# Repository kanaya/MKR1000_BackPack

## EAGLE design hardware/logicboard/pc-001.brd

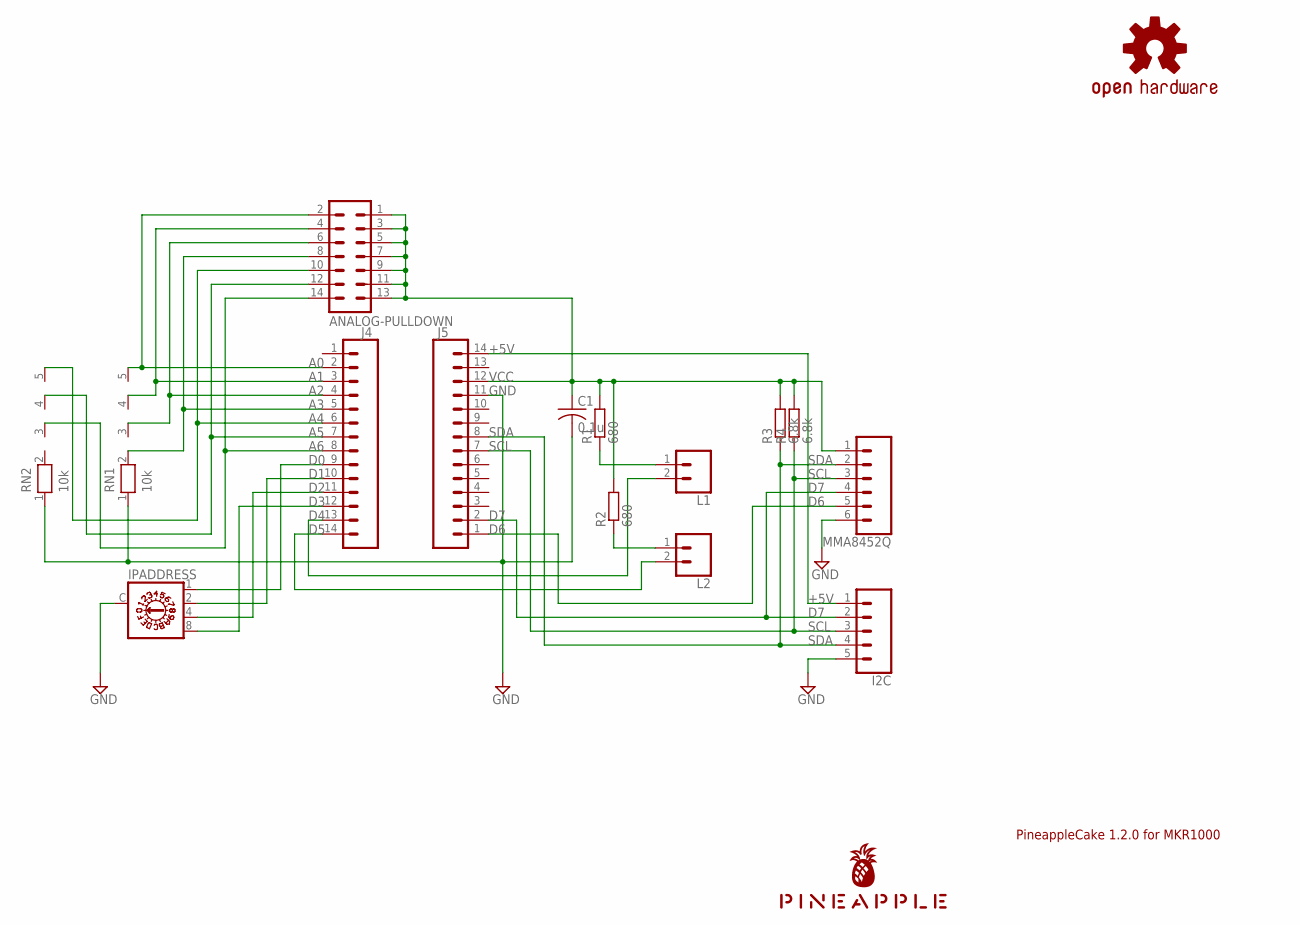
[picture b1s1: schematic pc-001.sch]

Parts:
ANALOG-PULLDOWN: ML14L
C1: 0.1u; C025-025X050
I2C: CONN_05SMD; 1X05_1MM
IPADDRESS: A1353HEX
J4, J5: DNP; 1X14
L1, L2: CONN_02-JST-2-PTH-NO_SILK; JST-2-PTH-NS
LOGO1: OSHW-LOGOS-COPPER; OSHW-LOGO-S_COPPER
MMA8452Q: CONN_06NO_SILK_FEMALE_PTH; 1X06_NO_SILK
R1, R2: 680; 0204/5
R3, R4: 6.8k; 0204/5
RN1, RN2: 10k; RN-5
U$1: PINEAPPLE450

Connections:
+5V: I2C.1, J5.14
A0: ANALOG-PULLDOWN.2, J4.2, RN1.5
A1: ANALOG-PULLDOWN.4, J4.3, RN1.4
A2: ANALOG-PULLDOWN.6, J4.4, RN1.3
A3: ANALOG-PULLDOWN.8, J4.5, RN1.2
A4: ANALOG-PULLDOWN.10, J4.6, RN2.5
A5: ANALOG-PULLDOWN.12, J4.7, RN2.4
A6: ANALOG-PULLDOWN.14, J4.8, RN2.3
D0: IPADDRESS.1, J4.9
D1: IPADDRESS.2, J4.10
D2: IPADDRESS.4, J4.11
D3: IPADDRESS.8, J4.12
D4: J4.13, L1.2
D5: J4.14, L2.2
D6: J5.1, MMA8452Q.5
D7: I2C.2, J5.2, MMA8452Q.4
GND: C1.2, I2C.5, IPADDRESS.C, J5.11, MMA8452Q.6, RN1.1, RN2.1
LED1A: L1.1, R1.1
LED2A: L2.1, R2.1
SCL: I2C.3, J5.7, MMA8452Q.3, R4.1
SDA: I2C.4, J5.6, J5.8, MMA8452Q.2, R3.1
VCC: ANALOG-PULLDOWN.1, ANALOG-PULLDOWN.3, ANALOG-PULLDOWN.5, ANALOG-PULLDOWN.7, ANALOG-PULLDOWN.9, ANALOG-PULLDOWN.11, ANALOG-PULLDOWN.13, C1.1, J5.12, MMA8452Q.1, R1.2, R2.2, R3.2, R4.2

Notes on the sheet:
PineappleCake 1.2.0 for MKR1000

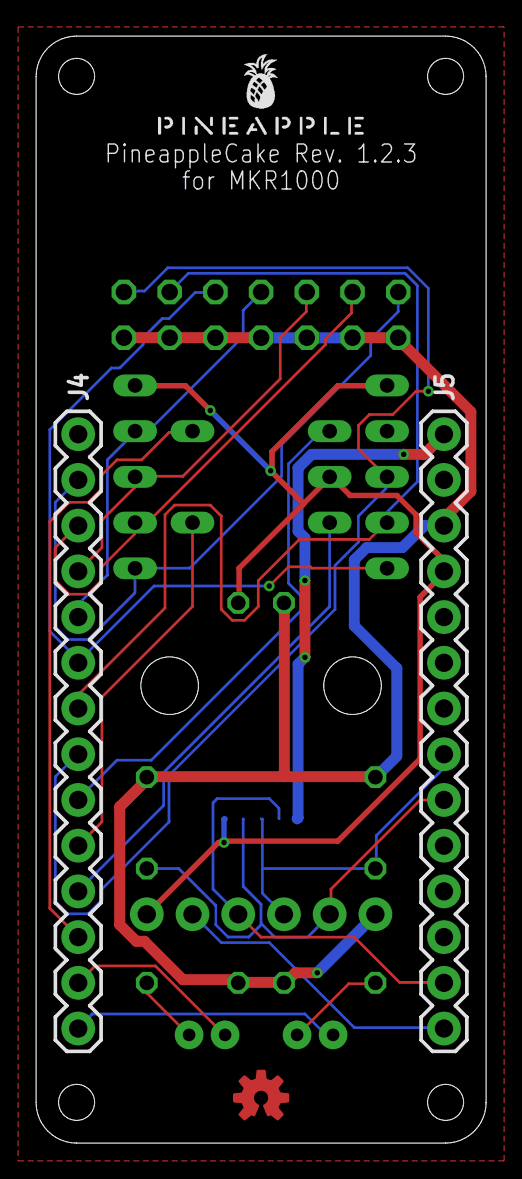
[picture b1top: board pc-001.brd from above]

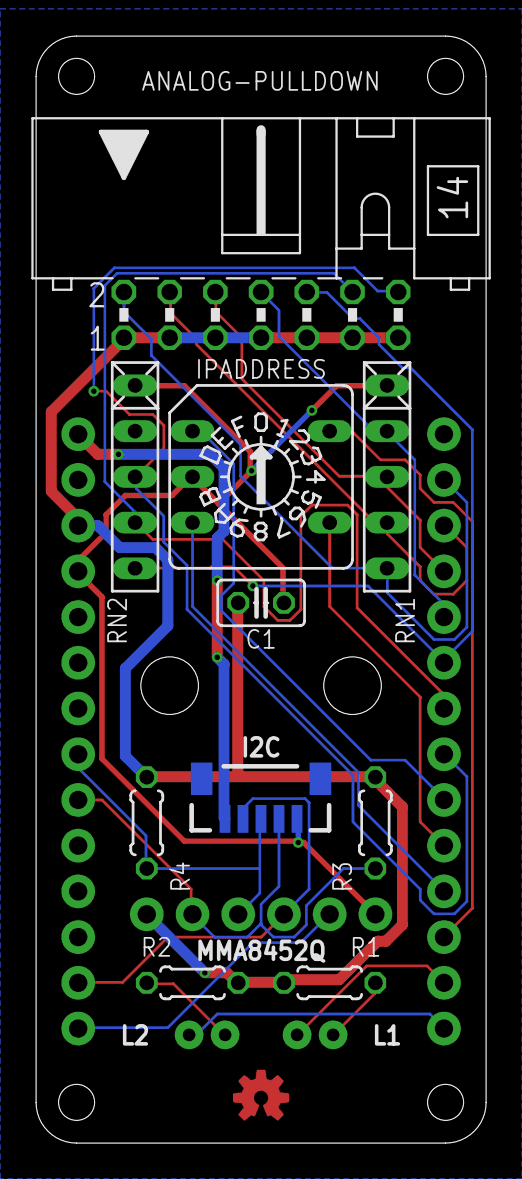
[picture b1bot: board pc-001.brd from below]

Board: 2 copper layers, 25.0 x 61.5 mm, 17 parts (13 on the bottom side), 22 nets.

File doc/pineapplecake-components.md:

# PineappleCake Components

| アイテム | 名前 | 規格 | 個数 | 購入先例 |
|--|--|--|--|--|
| 3軸加速度センサ | MMA8452Q | MMA8452Q | 1 | |
| 抵抗 | R1, R2 | 680 | 2 | |
| 抵抗 | R3, R4 | 6.8k | 2 | |
| 抵抗アレイ | RN1, RN2 | 4素子 10k | 2 | | 
| キャパシタ | C1 | 0.1u | 1 | |
| エンコーダスイッチ | IPADDRESS | 16進コンプリ | 1 | |
| コネクタ | Analog | ML14L | 1 | |
| コネクタ | J4, J5 | ピンヘッダ14p | 2 | |
| コネクタ | L1, L2 | PH 2p | 2 | |

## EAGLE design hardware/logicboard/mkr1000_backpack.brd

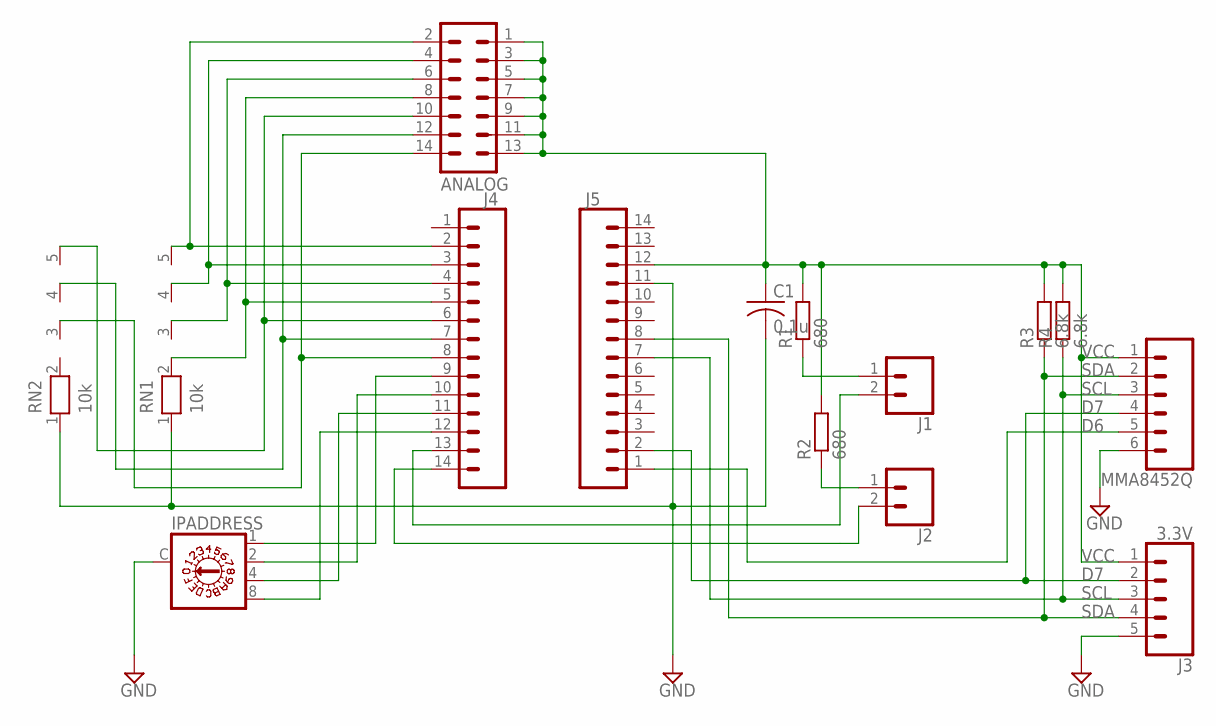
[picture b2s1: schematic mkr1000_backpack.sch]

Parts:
ANALOG: ML14L
C1: 0.1u; C025-025X050
IPADDRESS: A1353HEX
J1, J2: CONN_02-JST-2-PTH-NO_SILK; JST-2-PTH-NS
J3: 3.3V; 1X05_1MM
J4, J5: DNP; 1X14
MMA8452Q: CONN_06NO_SILK_FEMALE_PTH; 1X06_NO_SILK
R1, R2: 680; 0204/5
R3, R4: 6.8k; 0204/5
RN1, RN2: 10k; RN-5

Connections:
A0: ANALOG.2, J4.2, RN1.5
A1: ANALOG.4, J4.3, RN1.4
A2: ANALOG.6, J4.4, RN1.3
A3: ANALOG.8, J4.5, RN1.2
A4: ANALOG.10, J4.6, RN2.5
A5: ANALOG.12, J4.7, RN2.4
A6: ANALOG.14, J4.8, RN2.3
D0: IPADDRESS.1, J4.9
D1: IPADDRESS.2, J4.10
D2: IPADDRESS.4, J4.11
D3: IPADDRESS.8, J4.12
D6: J5.1, MMA8452Q.5
D7: J3.2, J5.2, MMA8452Q.4
GND: C1.2, IPADDRESS.C, J3.5, J5.11, MMA8452Q.6, RN1.1, RN2.1
unnamed: J1.1, R1.1
unnamed: J2.1, R2.1
unnamed: J1.2, J4.13
unnamed: J2.2, J4.14
SCL: J3.3, J5.7, MMA8452Q.3, R4.1
SDA: J3.4, J5.8, MMA8452Q.2, R3.1
VCC: ANALOG.1, ANALOG.3, ANALOG.5, ANALOG.7, ANALOG.9, ANALOG.11, ANALOG.13, C1.1, J3.1, J5.12, MMA8452Q.1, R1.2, R2.2, R3.2, R4.2

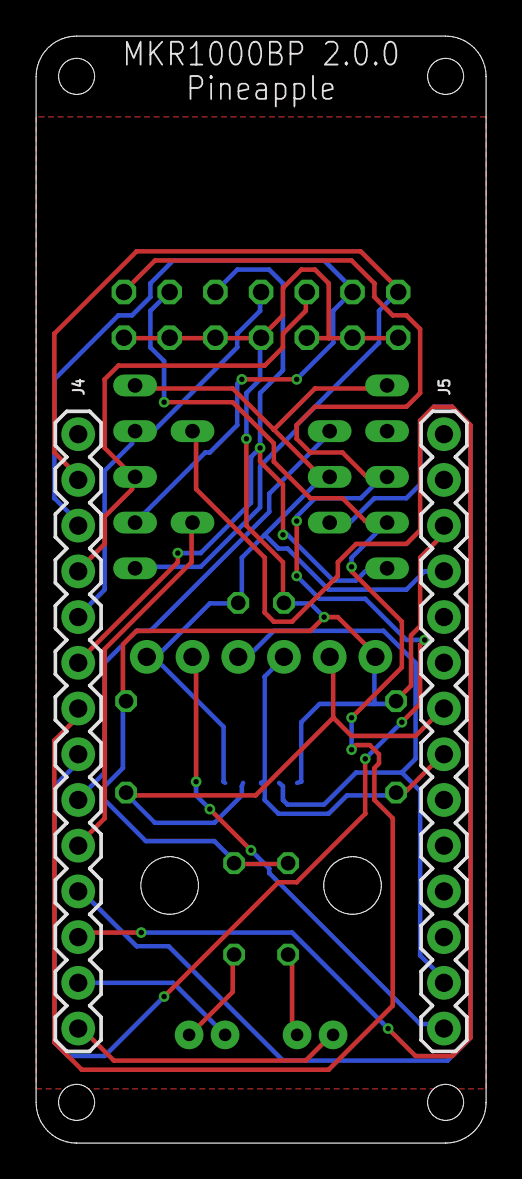
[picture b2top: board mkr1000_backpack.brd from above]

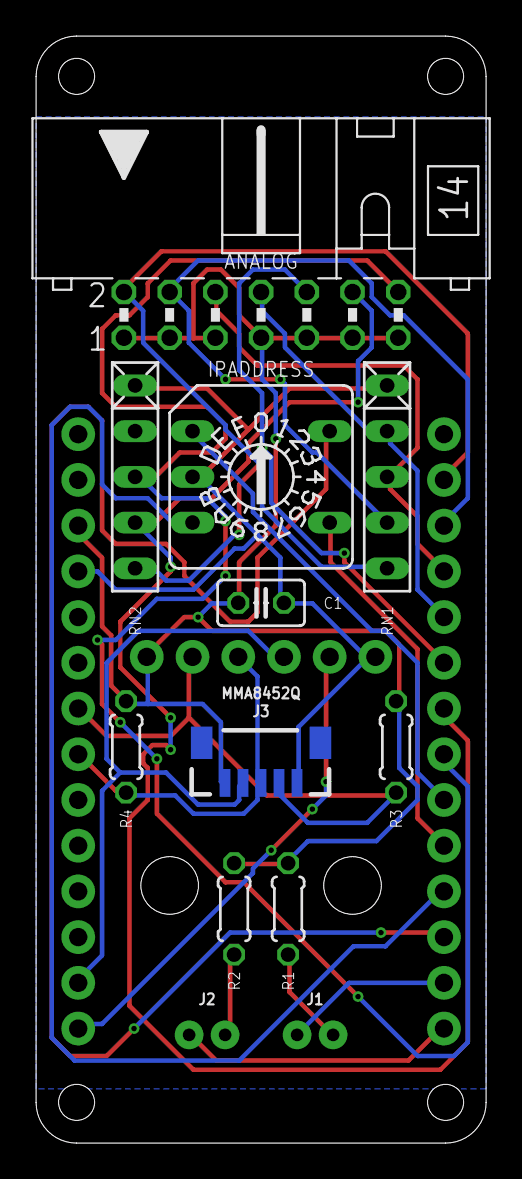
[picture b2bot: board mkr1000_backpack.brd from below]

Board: 2 copper layers, 25.0 x 61.5 mm, 15 parts (13 on the bottom side), 21 nets.

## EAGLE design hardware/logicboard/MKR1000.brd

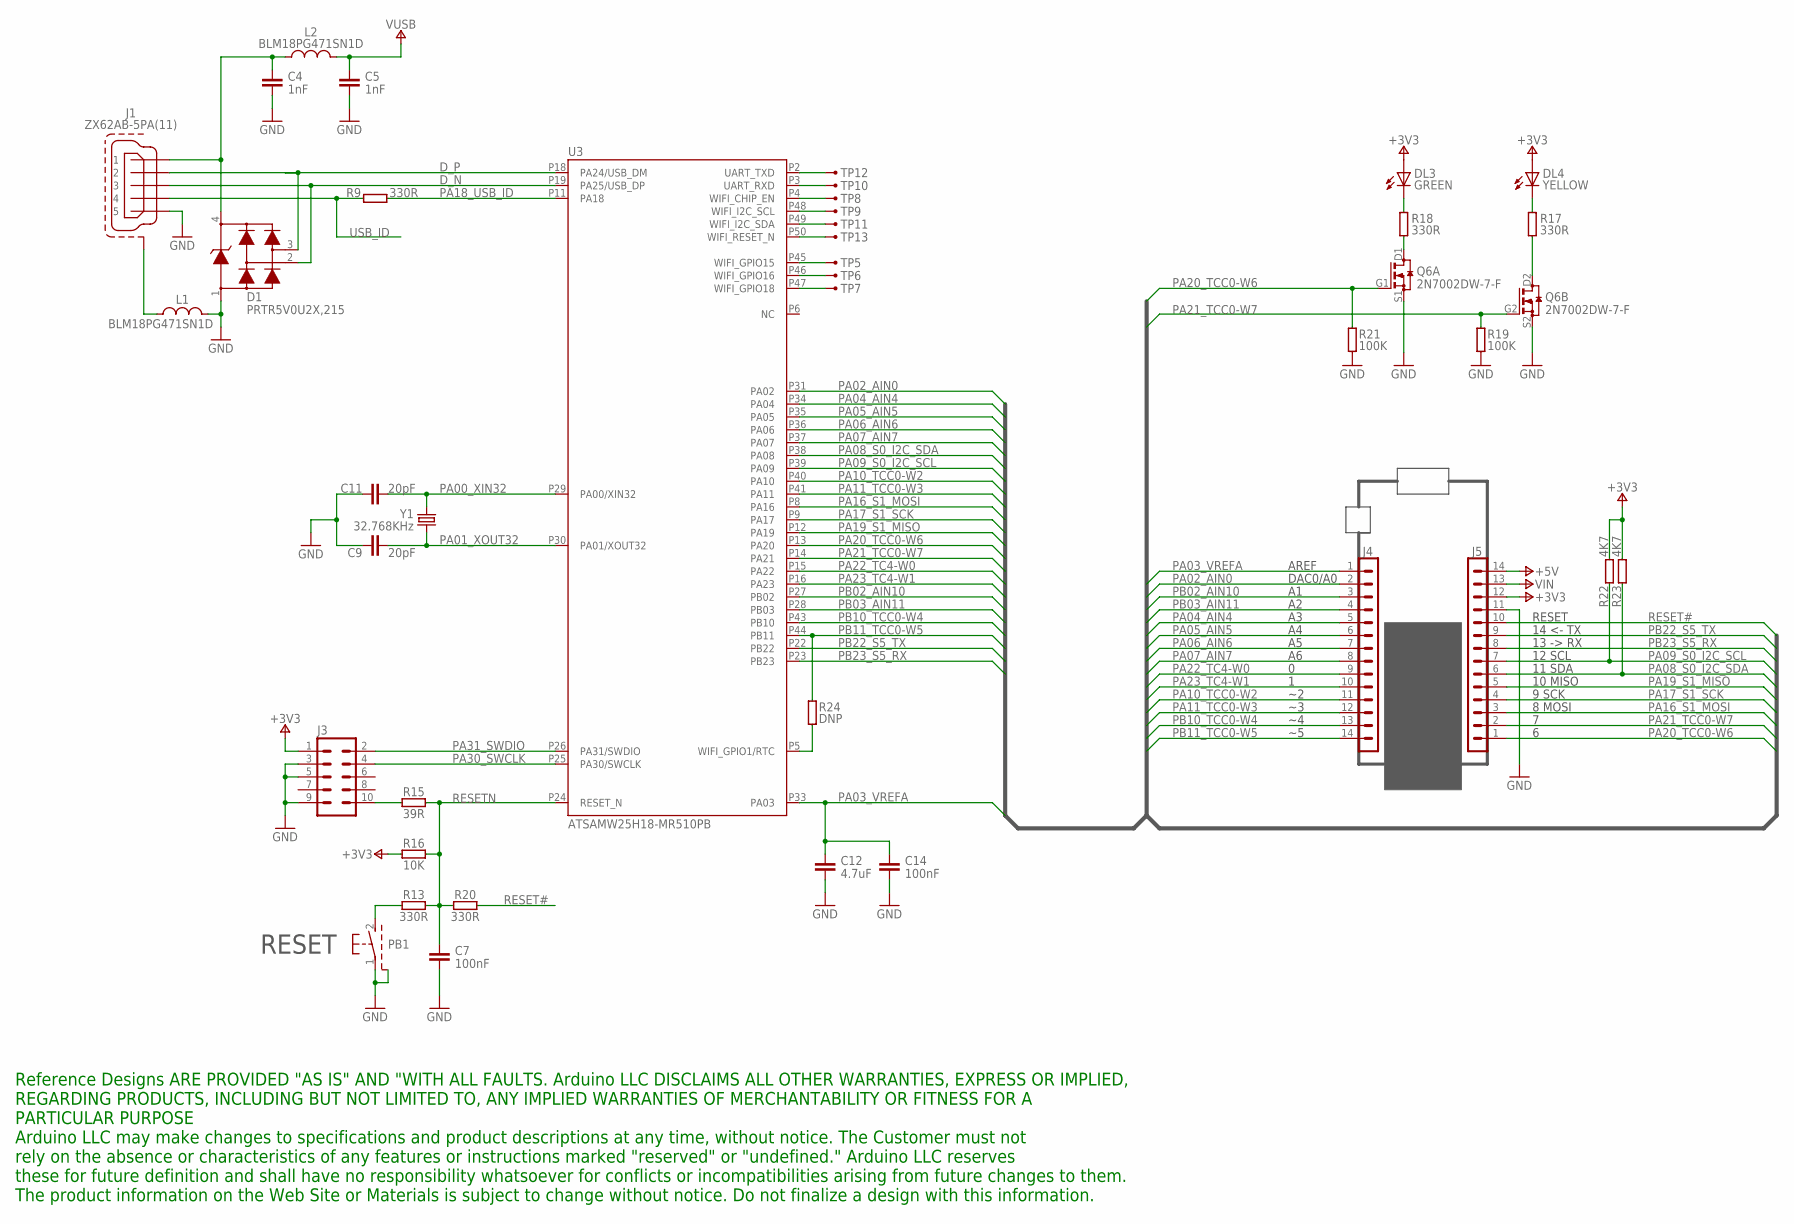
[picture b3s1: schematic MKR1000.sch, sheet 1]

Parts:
C4, C5: 1nF; 0402-1005X55N
C7, C14: 100nF; 0402-1005X55N
C9, C11: 20pF; 0402-1005X55N
C12: 4.7uF; 0402-1005X55N
D1: PRTR5V0U2X,215; SOT190P230X110-4N
DL3: GREEN; LEDC1608X80N-AK
DL4: YELLOW; LEDC1608X80N-AK
J1: ZX62AB-5PA(11); USBMICRO-ZX62-AB-5PA
J3: M50-3600542; FCI-MINITEK127HDR-10
J4, J5: DNP; STRIP-14-MODULI-A11
L1, L2: BLM18PG471SN1D; 0603-1608X90N
PB1: PTS820-20MM; PULS-45X29-PST820
Q6: 2N7002DW-7-F; SOT65P210X110-6AN-DM
R9, R13, R17, R18, R20: 330R; 0402-1005X55N
R15: 39R; 0402-1005X55N
R16: 10K; 0402-1005X55N
R19, R21: 100K; 0402-1005X55N
R22, R23: 4K7; 0402-1005X55N
R24: DNP; 0402-1005X55N
TP5, TP6, TP7, TP8, TP9, TP10, TP11, TP12, TP13: TESTPAD; PAD-SMD
U3: ATSAMW25H18-MR510PB; SAMW25
Y1: 32.768KHz; QUARZO-ABS07

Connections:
+3V3: DL3.A, DL4.A, J3.1, J5.12, R16.1, R22.2, R23.2; also elsewhere on the board
+5V: J5.14; also elsewhere on the board
D_N: D1.2, J1.3, U3.P19 (PA25/USB_DP)
D_P: D1.3, J1.2, U3.P18 (PA24/USB_DM)
GND: C4.2, C5.2, C7.2, C9.1, C11.1, C12.2, C14.2, D1.1, J1.5, J3.3, J3.5, J3.9, J5.11, L1.2, PB1.1, PB1.3 (SH), PB1.4 (SH), PB1.5 (SH), PB1.6 (SH), Q6.S1 (S), Q6.S2 (S), R19.1, R21.1; also elsewhere on the board
N17650912: C4.1, D1.4, J1.1, L2.1
unnamed: R24.1, U3.P5 (WIFI_GPIO1/RTC)
unnamed: DL4.C, R17.2
unnamed: Q6.D2 (D), R17.1
unnamed: Q6.D1 (D), R18.1
unnamed: J3.10, R15.1
unnamed: J1.6 (SH), J1.7 (SH), J1.8 (SH), J1.9 (SH), J1.10 (SH), J1.11 (SH), L1.1
unnamed: PB1.2 (S), R13.1
unnamed: DL3.C, R18.2
PA00_XIN32: C11.2, U3.P29 (PA00/XIN32), Y1.2
PA01_XOUT32: C9.2, U3.P30 (PA01/XOUT32), Y1.1
PA02_AIN0: J4.2, U3.P31 (PA02)
PA03_VREFA: C12.1, C14.1, J4.1, U3.P33 (PA03)
PA04_AIN4: J4.5, U3.P34 (PA04)
PA05_AIN5: J4.6, U3.P35 (PA05)
PA06_AIN6: J4.7, U3.P36 (PA06)
PA07_AIN7: J4.8, U3.P37 (PA07)
PA08_S0_I2C_SDA: J5.6, R23.1, U3.P38 (PA08)
PA09_S0_I2C_SCL: J5.7, R22.1, U3.P39 (PA09)
PA10_TCC0-W2: J4.11, U3.P40 (PA10)
PA11_TCC0-W3: J4.12, U3.P41 (PA11)
PA16_S1_MOSI: J5.3, U3.P8 (PA16)
PA17_S1_SCK: J5.4, U3.P9 (PA17)
PA18_USB_ID: R9.2, U3.P11 (PA18)
PA19_S1_MISO: J5.5, U3.P12 (PA19)
PA20_TCC0-W6: J5.1, Q6.G1 (G), R21.2, U3.P13 (PA20)
PA21_TCC0-W7: J5.2, Q6.G2 (G), R19.2, U3.P14 (PA21)
PA22_TC4-W0: J4.9, U3.P15 (PA22)
PA23_TC4-W1: J4.10, U3.P16 (PA23)
PA30_SWCLK: J3.4, U3.P25 (PA30/SWCLK)
PA31_SWDIO: J3.2, U3.P26 (PA31/SWDIO)
PB02_AIN10: J4.3, U3.P27 (PB02)
PB03_AIN11: J4.4, U3.P28 (PB03)
PB10_TCC0-W4: J4.13, U3.P43 (PB10)
PB11_TCC0-W5: J4.14, R24.2, U3.P44 (PB11)
PB22_S5_TX: J5.9, U3.P22 (PB22)
PB23_S5_RX: J5.8, U3.P23 (PB23)
RESET#: J5.10, R20.2
RESETN: C7.1, R13.2, R15.2, R16.2, R20.1, U3.P24 (RESET_N)
TP5: TP5.1, U3.P45 (WIFI_GPIO15)
TP6: TP6.1, U3.P46 (WIFI_GPIO16)
TP7: TP7.1, U3.P47 (WIFI_GPIO18)
TP8: TP8.1, U3.P4 (WIFI_CHIP_EN)
TP9: TP9.1, U3.P48 (WIFI_I2C_SCL)
TP10: TP10.1, U3.P3 (UART_RXD)
TP11: TP11.1, U3.P49 (WIFI_I2C_SDA)
TP12: TP12.1, U3.P2 (UART_TXD)
TP13: TP13.1, U3.P50 (WIFI_RESET_N)
USB_ID: J1.4, R9.1; also elsewhere on the board
VIN: J5.13; also elsewhere on the board
VUSB: C5.1, L2.2; also elsewhere on the board

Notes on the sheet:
14 <- TX
13 -> RX
12 SCL
RESET
11 SDA
8 MOSI
9 SCK
10 MISO
AREF
DAC0/A0
Reference Designs ARE PROVIDED "AS IS" AND "WITH ALL FAULTS. Arduino LLC DISCLAIMS ALL OTHER WARRANTIES, EXPRESS OR IMPLIED, REGARDING PRODUCTS, INCLUDING BUT NOT LIMITED TO, ANY IMPLIED WARRANTIES OF MERCHANTABILITY OR FITNESS FOR A PARTICULAR PURPOSE Arduino LLC may make changes to specifications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

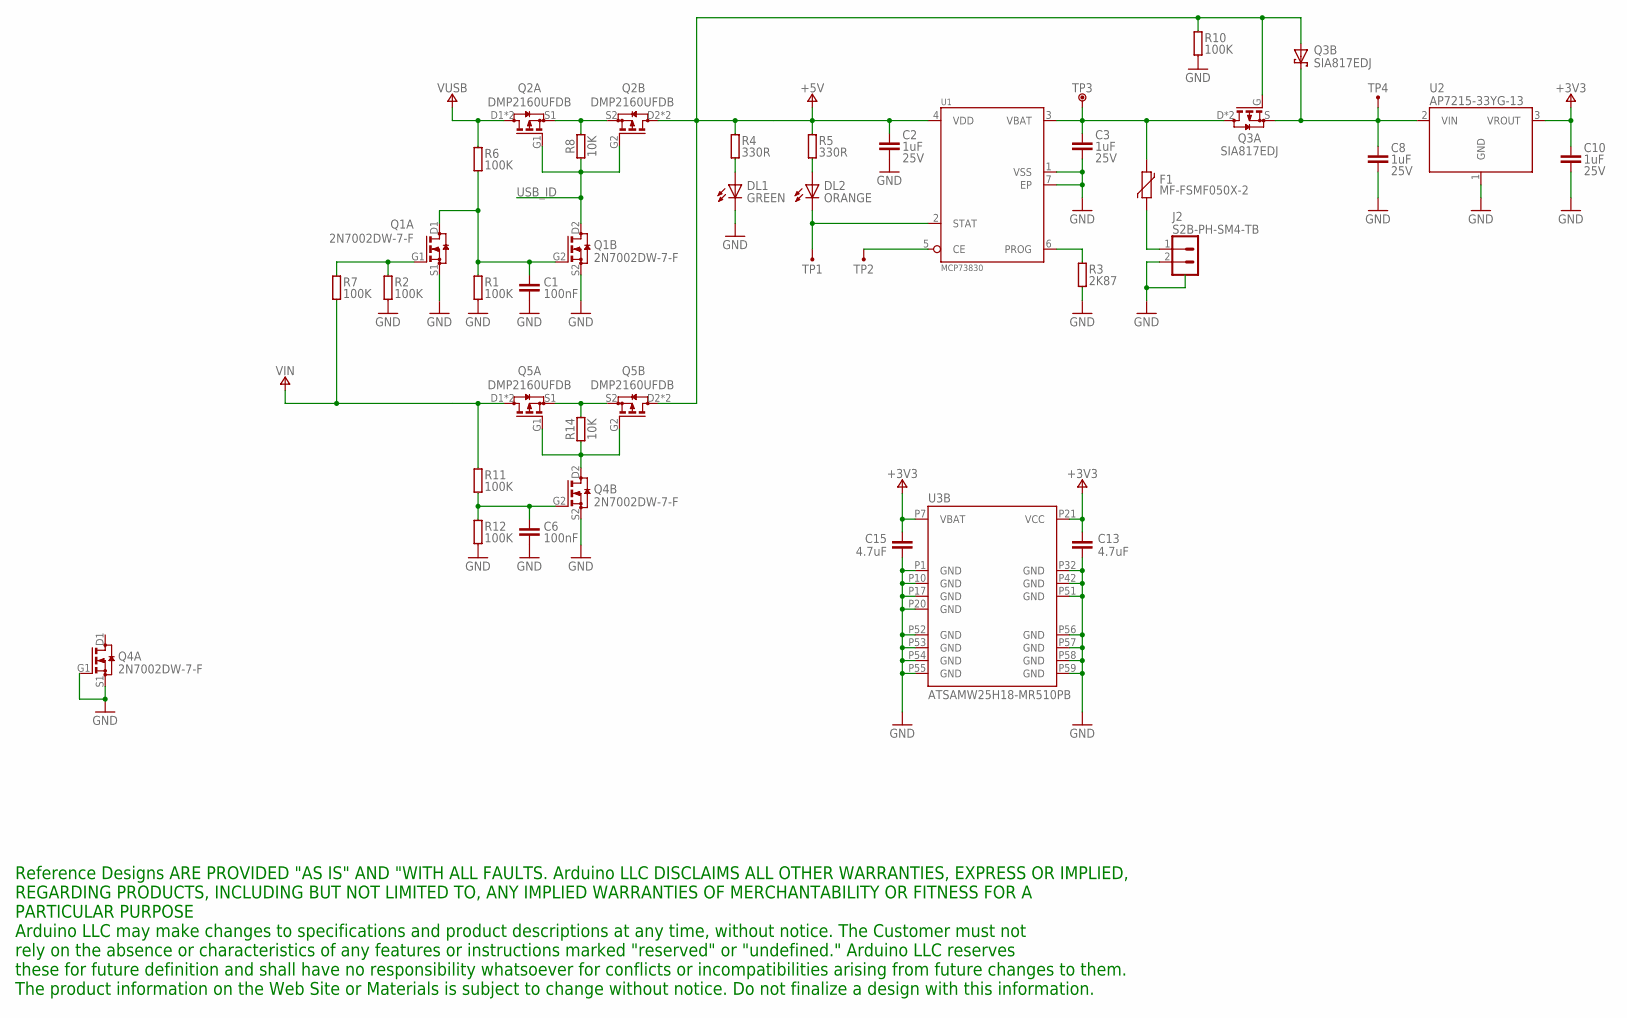
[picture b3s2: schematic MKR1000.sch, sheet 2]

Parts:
C1, C6: 100nF; 0402-1005X55N
C2, C3, C8, C10: 1uF; 0402-1005X55N; VOLTAGE 25V
C13, C15: 4.7uF; 0402-1005X55N
DL1: GREEN; LEDC1608X80N-AK
DL2: ORANGE; LEDC1608X80N-AK
F1: MF-FSMF050X-2; 0603-F1608X100N
J2: S2B-PH-SM4-TB; JST-S2B-PH-SM4-TB
Q1, Q4: 2N7002DW-7-F; SOT65P210X110-6AN-DM
Q2, Q5: DMP2160UFDB; SON65P200X200X60-8N-DM
Q3: SIA817EDJ; SON65P205X205X75-8N-MWSD
R1, R2, R6, R7, R10, R11, R12: 100K; 0402-1005X55N
R3: 2K87; 0805-R2013X50N
R4, R5: 330R; 0402-1005X55N
R8, R14: 10K; 0402-1005X55N
TP1, TP2, TP4: TESTPAD; PAD-SMD
TP3: TESTPOINT; TESTPOINT-60MLS-F0_9MM
U1: MCP73830; SON50P200X200X80-7N-EP160X60
U2: AP7215-33YG-13; SOT150P400X160-3N
U3: ATSAMW25H18-MR510PB; SAMW25

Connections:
+3V3: C10.1, C13.1, C15.1, U2.3 (VROUT), U3.P7 (VBAT), U3.P21 (VCC); also elsewhere on the board
+5V: C2.1, Q2.D2 (D), Q2.D2' (D), Q3.A, Q3.G, Q5.D2 (D), Q5.D2' (D), R4.2, R5.2, R10.2, U1.4 (VDD); also elsewhere on the board
GND: C1.2, C2.2, C3.2, C6.2, C8.2, C10.2, C13.2, C15.2, DL1.C, J2.2, J2.3 (SH), J2.4 (SH), Q1.S1 (S), Q1.S2 (S), Q4.G1 (G), Q4.S1 (S), Q4.S2 (S), R1.1, R2.1, R3.1, R10.1, R12.1, U1.1 (VSS), U1.7 (EP), U2.1 (GND), U3.P1 (GND), U3.P10 (GND), U3.P17 (GND), U3.P20 (GND), U3.P32 (GND), U3.P42 (GND), U3.P51 (GND), U3.P52 (GND), U3.P53 (GND), U3.P54 (GND), U3.P55 (GND), U3.P56 (GND), U3.P57 (GND), U3.P58 (GND), U3.P59 (GND); also elsewhere on the board
N17690335: Q2.S1 (S), Q2.S2 (S), R8.2
N17690381: C1.1, Q1.D1 (D), Q1.G2 (G), R1.2, R6.1
N17690428: Q1.G1 (G), R2.2, R7.2
N17690821: Q5.S1 (S), Q5.S2 (S), R14.2
N17690840: Q4.D2 (D), Q5.G1 (G), Q5.G2 (G), R14.1
N17690878: C6.1, Q4.G2 (G), R11.1, R12.2
N17699997: C8.1, Q3.K (C), Q3.K2 (C), Q3.S, TP4.1, U2.2 (VIN)
unnamed: DL2.C, TP1.1, U1.2 (STAT)
unnamed: DL1.A, R4.1
unnamed: R3.2, U1.6 (PROG)
unnamed: DL2.A, R5.1
unnamed: F1.1, J2.1
unnamed: TP2.1, U1.5 (CE)
USB_ID: Q1.D2 (D), Q2.G1 (G), Q2.G2 (G), R8.1; also elsewhere on the board
VBATT: C3.1, F1.2, Q3.D, Q3.D2 (D), TP3.1, U1.3 (VBAT)
VIN: Q5.D1 (D), Q5.D1' (D), R7.1, R11.2; also elsewhere on the board
VUSB: Q2.D1 (D), Q2.D1' (D), R6.2; also elsewhere on the board

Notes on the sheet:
Reference Designs ARE PROVIDED "AS IS" AND "WITH ALL FAULTS. Arduino LLC DISCLAIMS ALL OTHER WARRANTIES, EXPRESS OR IMPLIED, REGARDING PRODUCTS, INCLUDING BUT NOT LIMITED TO, ANY IMPLIED WARRANTIES OF MERCHANTABILITY OR FITNESS FOR A PARTICULAR PURPOSE Arduino LLC may make changes to specifications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

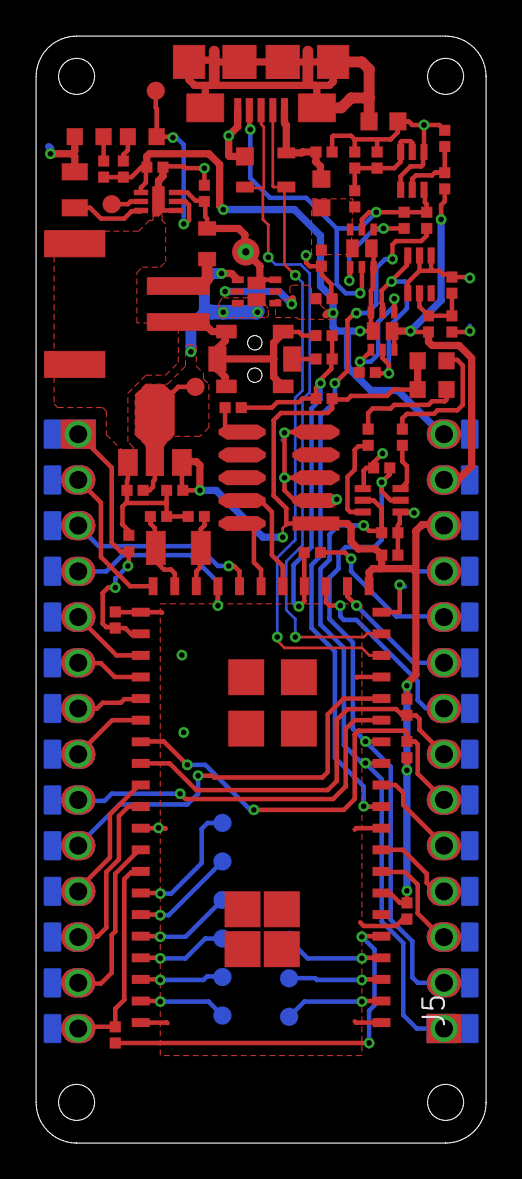
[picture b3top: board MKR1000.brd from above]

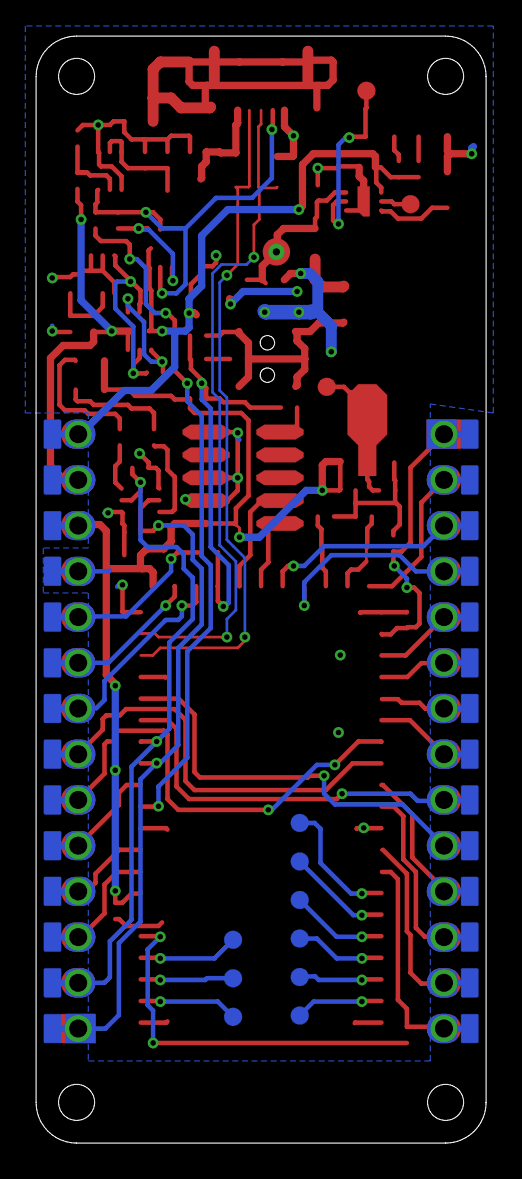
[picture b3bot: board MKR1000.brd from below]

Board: 2 copper layers, 25.0 x 61.5 mm, 76 parts (9 on the bottom side), 70 nets.

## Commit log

2018-08-05 Imported MKR1000 board.
2018-08-05 Removed everything but pinheaders.
2018-08-05 Analog pins.
2018-08-05 First try.
2018-08-05 Second try. Looks good.
2018-08-05 Backside mounting.
2018-08-05 Added encoder switch for selecting IP address.
2018-08-05 Moved 10p MIL connector up by 1mm.
2018-08-05 Capacitor.
2018-08-06 LED ports and I2C port.
2018-08-06 SparkFun Triple Axis Accelerometer Breakout - H3LIS331DL Ready.
2018-08-06 MMA8452Q
2018-08-06 Fixed position of pinheader.
2018-08-11 Name change.
2018-08-11 Filename change.
2018-08-11 GND pattern.
2018-08-11 OSHW logo.
2018-08-13 Pineapple logo v2.
2018-08-13 New pineapple logo.
2018-08-14 Updated silk pattern.
2018-08-14 Changed signal names.
2018-08-14 Added Makefile.
2018-08-14 Version number 1.0.0 -> 2.0.0.
2018-08-16 MKR1000BP -> PineappleCake.
2018-08-16 New Pineapple Logo was put on the board.
2018-08-16 14p Analog input.
2018-08-16 Layout of Analog input.
2018-08-16 Routing.
2018-08-17 Changed silk pattern of version number (1.0.1).
2018-08-17 Changed silk pattern of version number (1.1.0).
2018-08-17 Changed silk pattern of version number (1.2.0).
2018-08-17 Moved "Analog" silk.
2018-08-20 Changed Pineapple Logo from Vector-based to Bitmap-based.
2018-08-21 OSHW logo (silk -> copper).
2018-08-21 Pineapple Logo (vector -> bitmap), OSHW Logo (silk -> copper).
2018-08-21 Flipped I2C connector.
2018-08-21 Fixed error of version number on the schematic.
2018-08-21 Flipped I2C connector (again).
2018-08-22 Changed font size of silk patterns.
2018-09-15 Rerouted.
2018-09-15 Route update.
2018-09-15 Added images.
2018-09-16 Moved document dir.
2018-09-16 Image update.
2018-09-16 1st pin of I2C connector now has 5V supply, not 3.3V.
2018-09-16 Removed Makefile.
2018-09-16 document->doc.
2018-09-16 Updated README.
2018-09-16 Added component list.
2018-09-16 Fixed doc.
2018-09-18 Removed part list.
2018-09-21 Hotfix. I2C connector is now connected to +5V, not +3.3V (Vcc).
2018-10-15 Fixed wrong connection to MMA8452Q.
2018-10-26 Fixed positioning of MMA8452Q.
2019-01-13 Fixed connection of SDA.
2019-01-13 Fixed revision number on the board.

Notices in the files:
parts and their libraries:
SparkFun-Connectors: Licensing: Creative Commons ShareAlike 4.0 International - https://creativecommons.org/licenses/by-sa/4.0
